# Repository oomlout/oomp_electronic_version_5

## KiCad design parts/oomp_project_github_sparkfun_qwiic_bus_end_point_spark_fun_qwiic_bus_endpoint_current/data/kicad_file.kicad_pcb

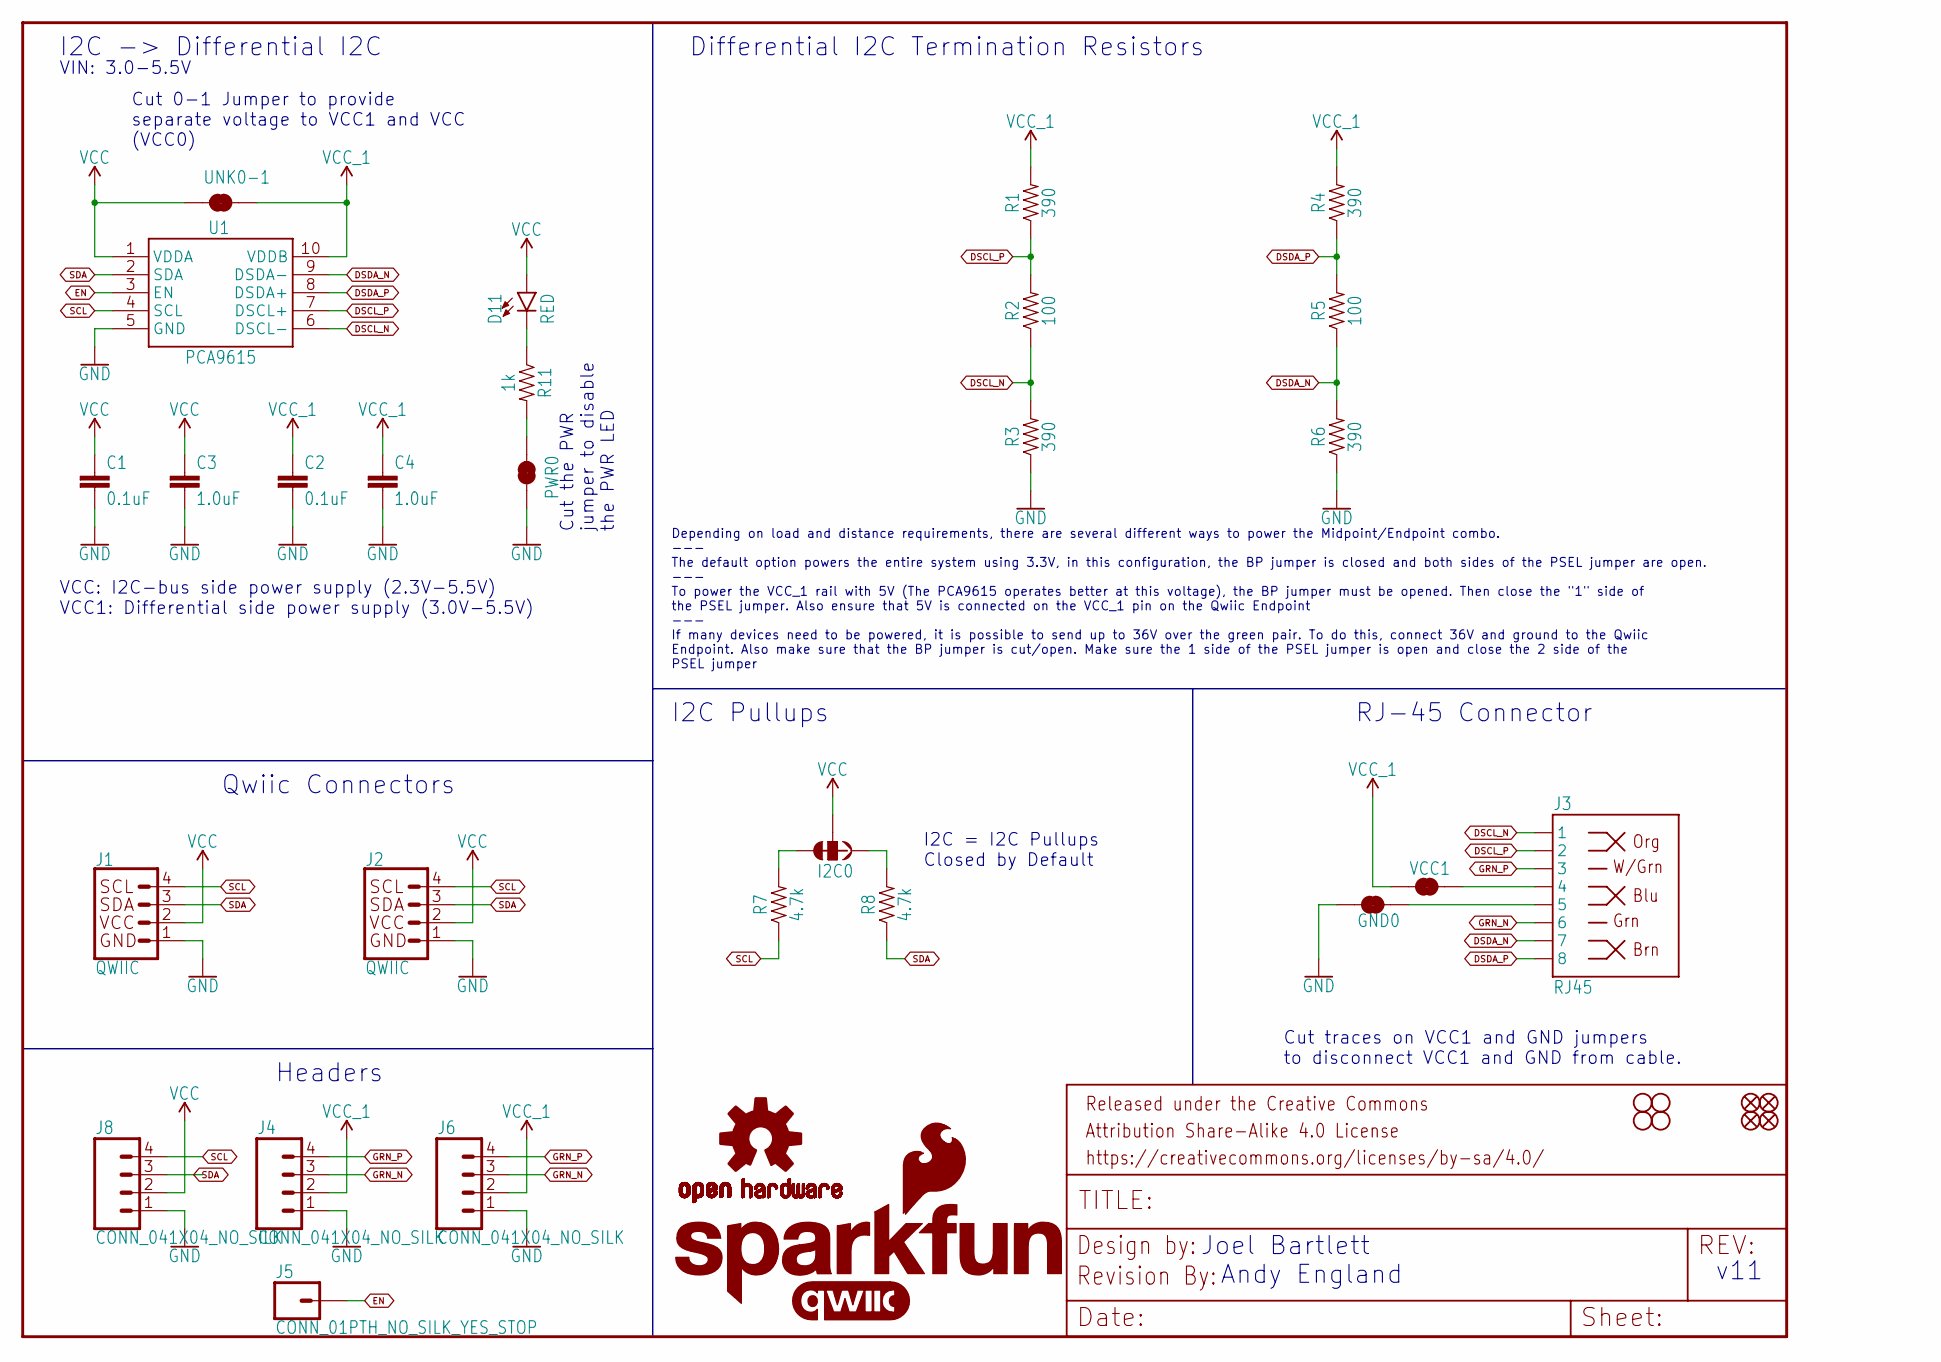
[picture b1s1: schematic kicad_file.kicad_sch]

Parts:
C1, C2: 0.1uF; 0603
C3, C4: 1.0uF; 0603
D11: RED; LED-0603
FD1, FD2, FD3, FD4: FIDUCIALUFIDUCIAL; FIDUCIAL-MICRO
FRAME1: FRAME-LETTER; CREATIVE_COMMONS
GND0: JUMPER-SMT_2_NC_TRACE_SILK; SMT-JUMPER_2_NC_TRACE_SILK
H1, H2, H3, H4: STAND-OFF
I2C0: JUMPER-SMT_3_2-NC_TRACE_SILK; SMT-JUMPER_3_2-NC_TRACE_SILK
J1, J2: QWIIC; JST04_1MM_RA
J3: RJ45; RJ45-8
J4, J6, J8: CONN_041X04_NO_SILK; 1X04_NO_SILK
J5: CONN_01PTH_NO_SILK_YES_STOP; 1X01_NO_SILK
LOGO1: OSHW-LOGOM; OSHW-LOGO-M
LOGO2: REVISION
LOGO3: QWIIC_LOGO_4MM; QWIIC_4MM
LOGO4: SFE_LOGO_NAME_FLAME.1_INCH; SFE_LOGO_NAME_FLAME_.1
LOGO5: SFE_LOGO_FLAME.1_INCH; SFE_LOGO_FLAME_.1
PWR0: JUMPER-SMT_2_NC_TRACE_SILK; SMT-JUMPER_2_NC_TRACE_SILK
R1, R3, R4, R6: 390; 0603
R2, R5: 100; 0603
R7, R8: 4.7k; 0603
R11: 1k; 0603
U1: PCA9615; TSSOP10
UNK0-1: JUMPER-SMT_2_NC_TRACE_SILK; SMT-JUMPER_2_NC_TRACE_SILK
VCC1: JUMPER-SMT_2_NC_TRACE_SILK; SMT-JUMPER_2_NC_TRACE_SILK

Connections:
DSCL_N: J3.1, R2.1, R3.2, U1.6 (DSCL-)
DSCL_P: J3.2, R1.1, R2.2, U1.7 (DSCL+)
DSDA_N: J3.7, R5.1, R6.2, U1.9 (DSDA-)
DSDA_P: J3.8, R4.1, R5.2, U1.8 (DSDA+)
EN: J5.1, U1.3 (EN)
GND: C1.2, C2.2, C3.2, C4.2, GND0.1, J1.1, J2.1, J4.1, J6.1, J8.1, PWR0.1, R3.1, R6.1, U1.5 (GND)
GRN_N: J3.6, J4.3, J6.3
GRN_P: J3.3, J4.4, J6.4
unnamed: J3.4, VCC1.2
unnamed: GND0.2, J3.5
unnamed: I2C0.1, R8.2
unnamed: I2C0.3, R7.2
unnamed: D11.C, R11.1
unnamed: PWR0.2, R11.2
SCL: J1.4, J2.4, J8.4, R7.1, U1.4 (SCL)
SDA: J1.3, J2.3, J8.3, R8.1, U1.2 (SDA)
VCC: C1.1, C3.1, D11.A, I2C0.2, J1.2, J2.2, J8.2, U1.1 (VDDA), UNK0-1.2
VCC_1: C2.1, C4.1, J4.2, J6.2, R1.2, R4.2, U1.10 (VDDB), UNK0-1.1, VCC1.1

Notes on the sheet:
Cut 0-1 Jumper to provide separate voltage to VCC1 and VCC (VCC0)
Joel Bartlett
VIN: 3.0-5.5V
I2C -> Differential I2C
RJ-45 Connector
Depending on load and distance requirements, there are several different ways to power the Midpoint/Endpoint combo. --- The default option powers the entire system using 3.3V, in this configuration, the BP jumper is closed and both sides of the PSEL jumper are open. --- To power the VCC_1 rail with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
Andy England
Qwiic Connectors
VCC: I2C-bus side power supply (2.3V-5.5V) VCC1: Differential side power supply (3.0V-5.5V)
Cut traces on VCC1 and GND jumpers to disconnect VCC1 and GND from cable.
Cut the PWR jumper to disable the PWR LED
Differential I2C Termination Resistors
Headers
I2C Pullups
v11
I2C = I2C Pullups Closed by Default

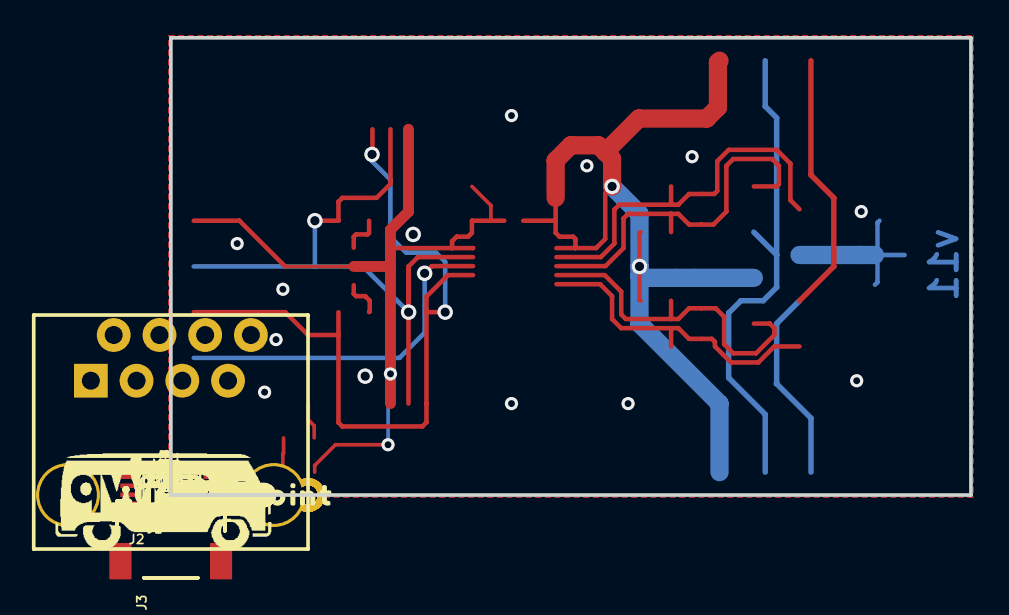
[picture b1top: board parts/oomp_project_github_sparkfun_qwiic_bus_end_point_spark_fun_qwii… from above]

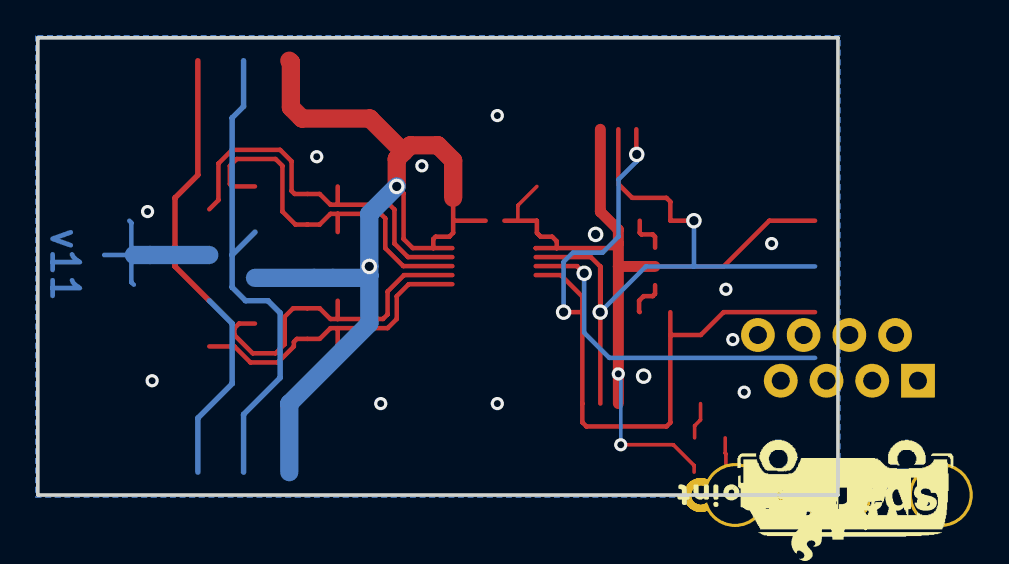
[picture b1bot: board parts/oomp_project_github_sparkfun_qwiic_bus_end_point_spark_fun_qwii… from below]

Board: 2 copper layers, 44.5 x 25.4 mm, 76 parts (23 on the bottom side), 18 nets.

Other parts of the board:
U$1: I2C
U$2, U$29: GRN0
U$3, U$4, U$5, U$6, U$13, U$33, U$34: #GND#0
U$7, U$8: #3V3#0
U$9, U$15: #SDA#0
U$10, U$16: #SCL#0
U$11, U$17: #EN#0
U$12: #VDDA#0
U$14, U$18: #GND2#0
U$19, U$22: #GRNW#0
U$20, U$21, U$31, U$32: #VCC1#0
U$23, U$28: QWIICBUS#WORKING#LOGO#JPG
U$24, U$30: #VCC2#0
U$25: 0#10
U$26, U$35: ENDPOINT0
U$27: PWR0

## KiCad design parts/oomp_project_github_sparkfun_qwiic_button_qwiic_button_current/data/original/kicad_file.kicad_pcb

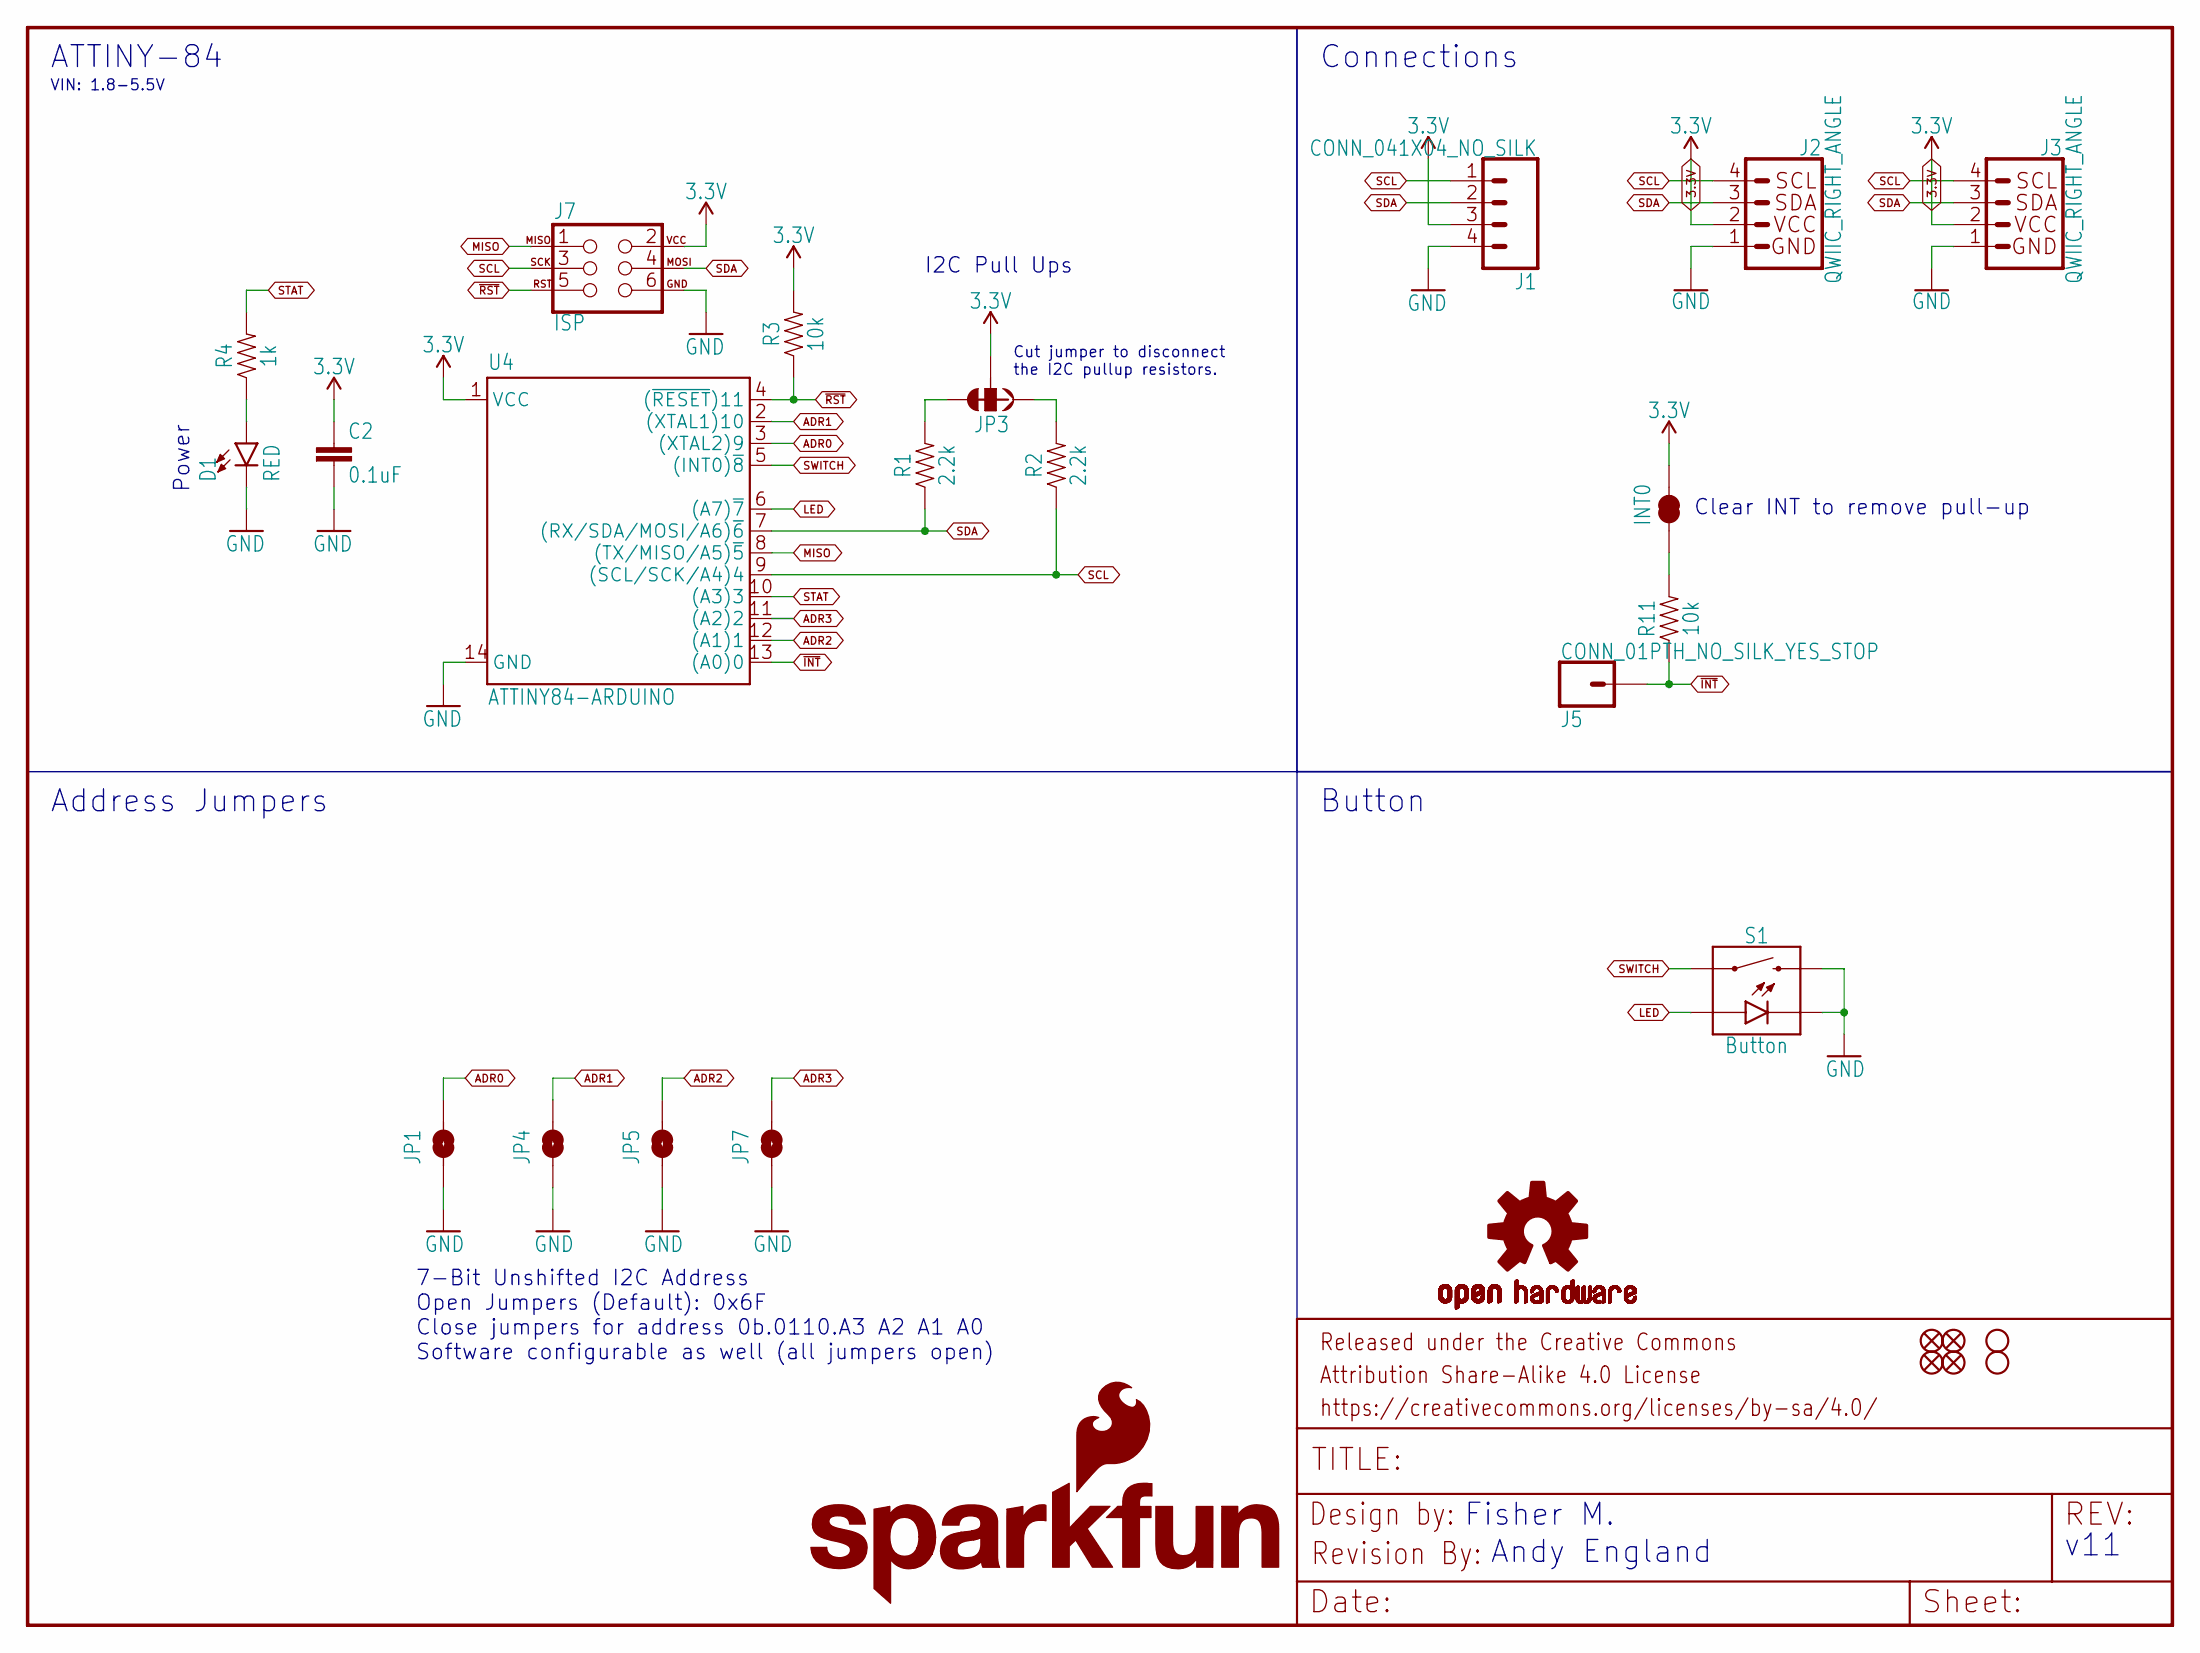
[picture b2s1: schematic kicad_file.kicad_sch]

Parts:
C2: 0.1uF; 0603
D1: RED; LED-0603
FRAME1: FRAME-LETTER; CREATIVE_COMMONS
H1, H2: STAND-OFF
INT0: JUMPER-SMT_2_NC_TRACE_SILK; SMT-JUMPER_2_NC_TRACE_SILK
J1: CONN_041X04_NO_SILK; 1X04_NO_SILK
J2, J3: QWIIC_RIGHT_ANGLE; JST04_1MM_RA
J5: CONN_01PTH_NO_SILK_YES_STOP; 1X01_NO_SILK
J7: ISP; 2X3_TEST_POINTS
JP1, JP4, JP5, JP7: JUMPER-SMT_2_NO_NO-SILK; SMT-JUMPER_2_NO_NO-SILK
JP2, JP6, JP8, JP9: FIDUCIALUFIDUCIAL; MICRO-FIDUCIAL
JP3: JUMPER-SMT_3_2-NC_TRACE_SILK; SMT-JUMPER_3_2-NC_TRACE_SILK
LOGO1: OSHW-LOGOMINI; OSHW-LOGO-MINI
LOGO2: REVISION
LOGO3: SFE_LOGO_NAME.1_INCH; SFE_LOGO_NAME_.1
LOGO4: SFE_LOGO_FLAME.1_INCH; SFE_LOGO_FLAME_.1
R1, R2: 2.2k; 0603
R3, R11: 10k; 0603
R4: 1k; 0603
S1: Button; TACTILE_SWITCH_LED_PTH_12MM
U4: ATTINY84-ARDUINO; SO14

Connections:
3.3V: C2.1, INT0.2, J1.3, J2.2, J3.2, J7.2, JP3.2, R3.2, U4.1 (VCC)
ADR0: JP1.2, U4.3 ((XTAL2)9)
ADR1: JP4.2, U4.2 ((XTAL1)10)
ADR2: JP5.2, U4.12 ((A1)1)
ADR3: JP7.2, U4.11 ((A2)2)
GND: C2.2, D1.C, J1.4, J2.1, J3.1, J7.6, JP1.1, JP4.1, JP5.1, JP7.1, S1.2, S1.C, U4.14 (GND)
INT_R: INT0.1, R11.2
LED: S1.A, U4.6 ((A7)~7)
MISO: J7.1, U4.8 ((TX/MISO/A5)~5)
unnamed: D1.A, R4.1
SCL: J1.1, J2.4, J3.4, J7.3, R2.1, U4.9 ((SCL/SCK/A4)4)
SCL_PU1: JP3.1, R2.2
SDA: J1.2, J2.3, J3.3, J7.4, R1.1, U4.7 ((RX/SDA/MOSI/A6)~6)
SDA_PU1: JP3.3, R1.2
STAT: R4.2, U4.10 ((A3)3)
SWITCH: S1.4 (1), U4.5 ((INT0)~8)
~INT: J5.1, R11.1, U4.13 ((A0)0)
~RST: J7.5, R3.1, U4.4 ((~RESET)11)

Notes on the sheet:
Andy England
Fisher M.
7-Bit Unshifted I2C Address Open Jumpers (Default): 0x6F Close jumpers for address 0b.0110.A3 A2 A1 A0 Software configurable as well (all jumpers open)
I2C Pull Ups
Cut jumper to disconnect the I2C pullup resistors.
Clear INT to remove pull-up
ATTINY-84
VIN: 1.8-5.5V
Button
Power
Address Jumpers
v11
Connections

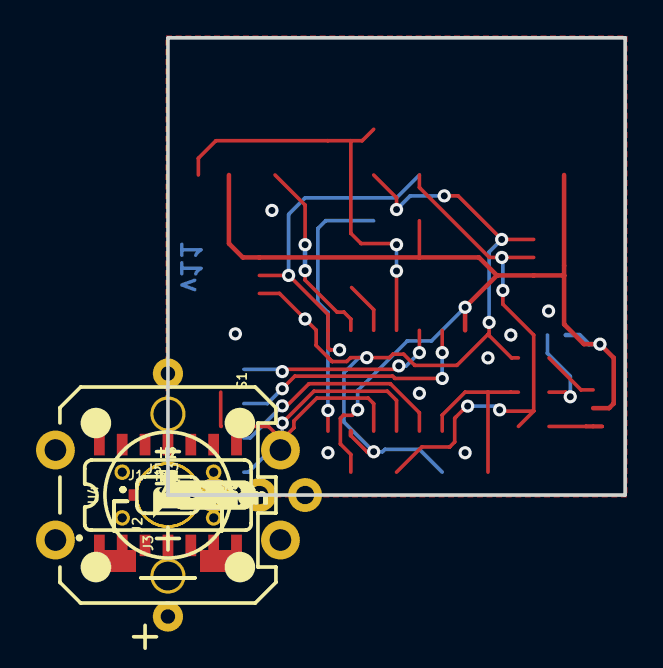
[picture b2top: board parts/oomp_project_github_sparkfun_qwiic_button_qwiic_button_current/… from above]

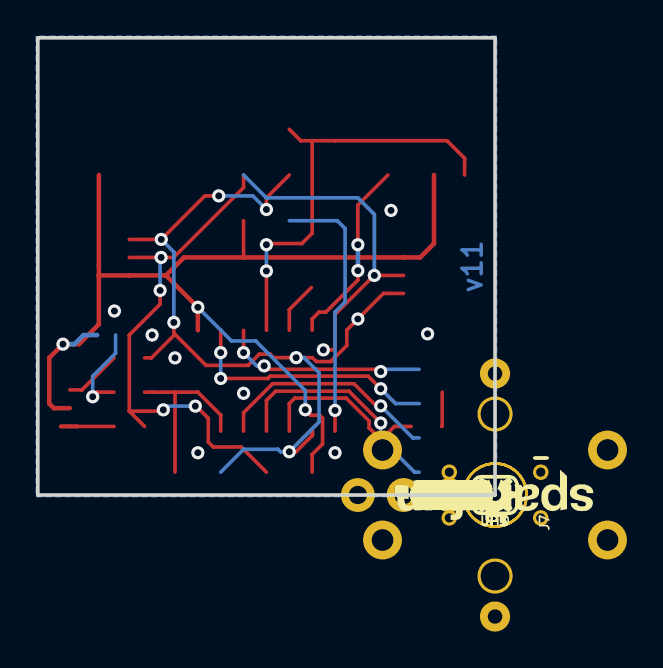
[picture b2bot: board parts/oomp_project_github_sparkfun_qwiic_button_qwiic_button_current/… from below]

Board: 2 copper layers, 25.4 x 25.4 mm, 48 parts (23 on the bottom side), 18 nets.

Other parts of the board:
U$1, U$2: BUTTON1
U$3: PWR-()-04
U$4: INT-()-04
U$5: SCL
U$6: SDA
U$7: 3.3V
U$8: GND
U$9: (ADR)
U$10: I_SUPER2_C-()-03
U$15: INT#-[_-04
U$16: A00
U$17: A11
U$19: A22
U$20, U$23: QWIIC0
U$21: A33

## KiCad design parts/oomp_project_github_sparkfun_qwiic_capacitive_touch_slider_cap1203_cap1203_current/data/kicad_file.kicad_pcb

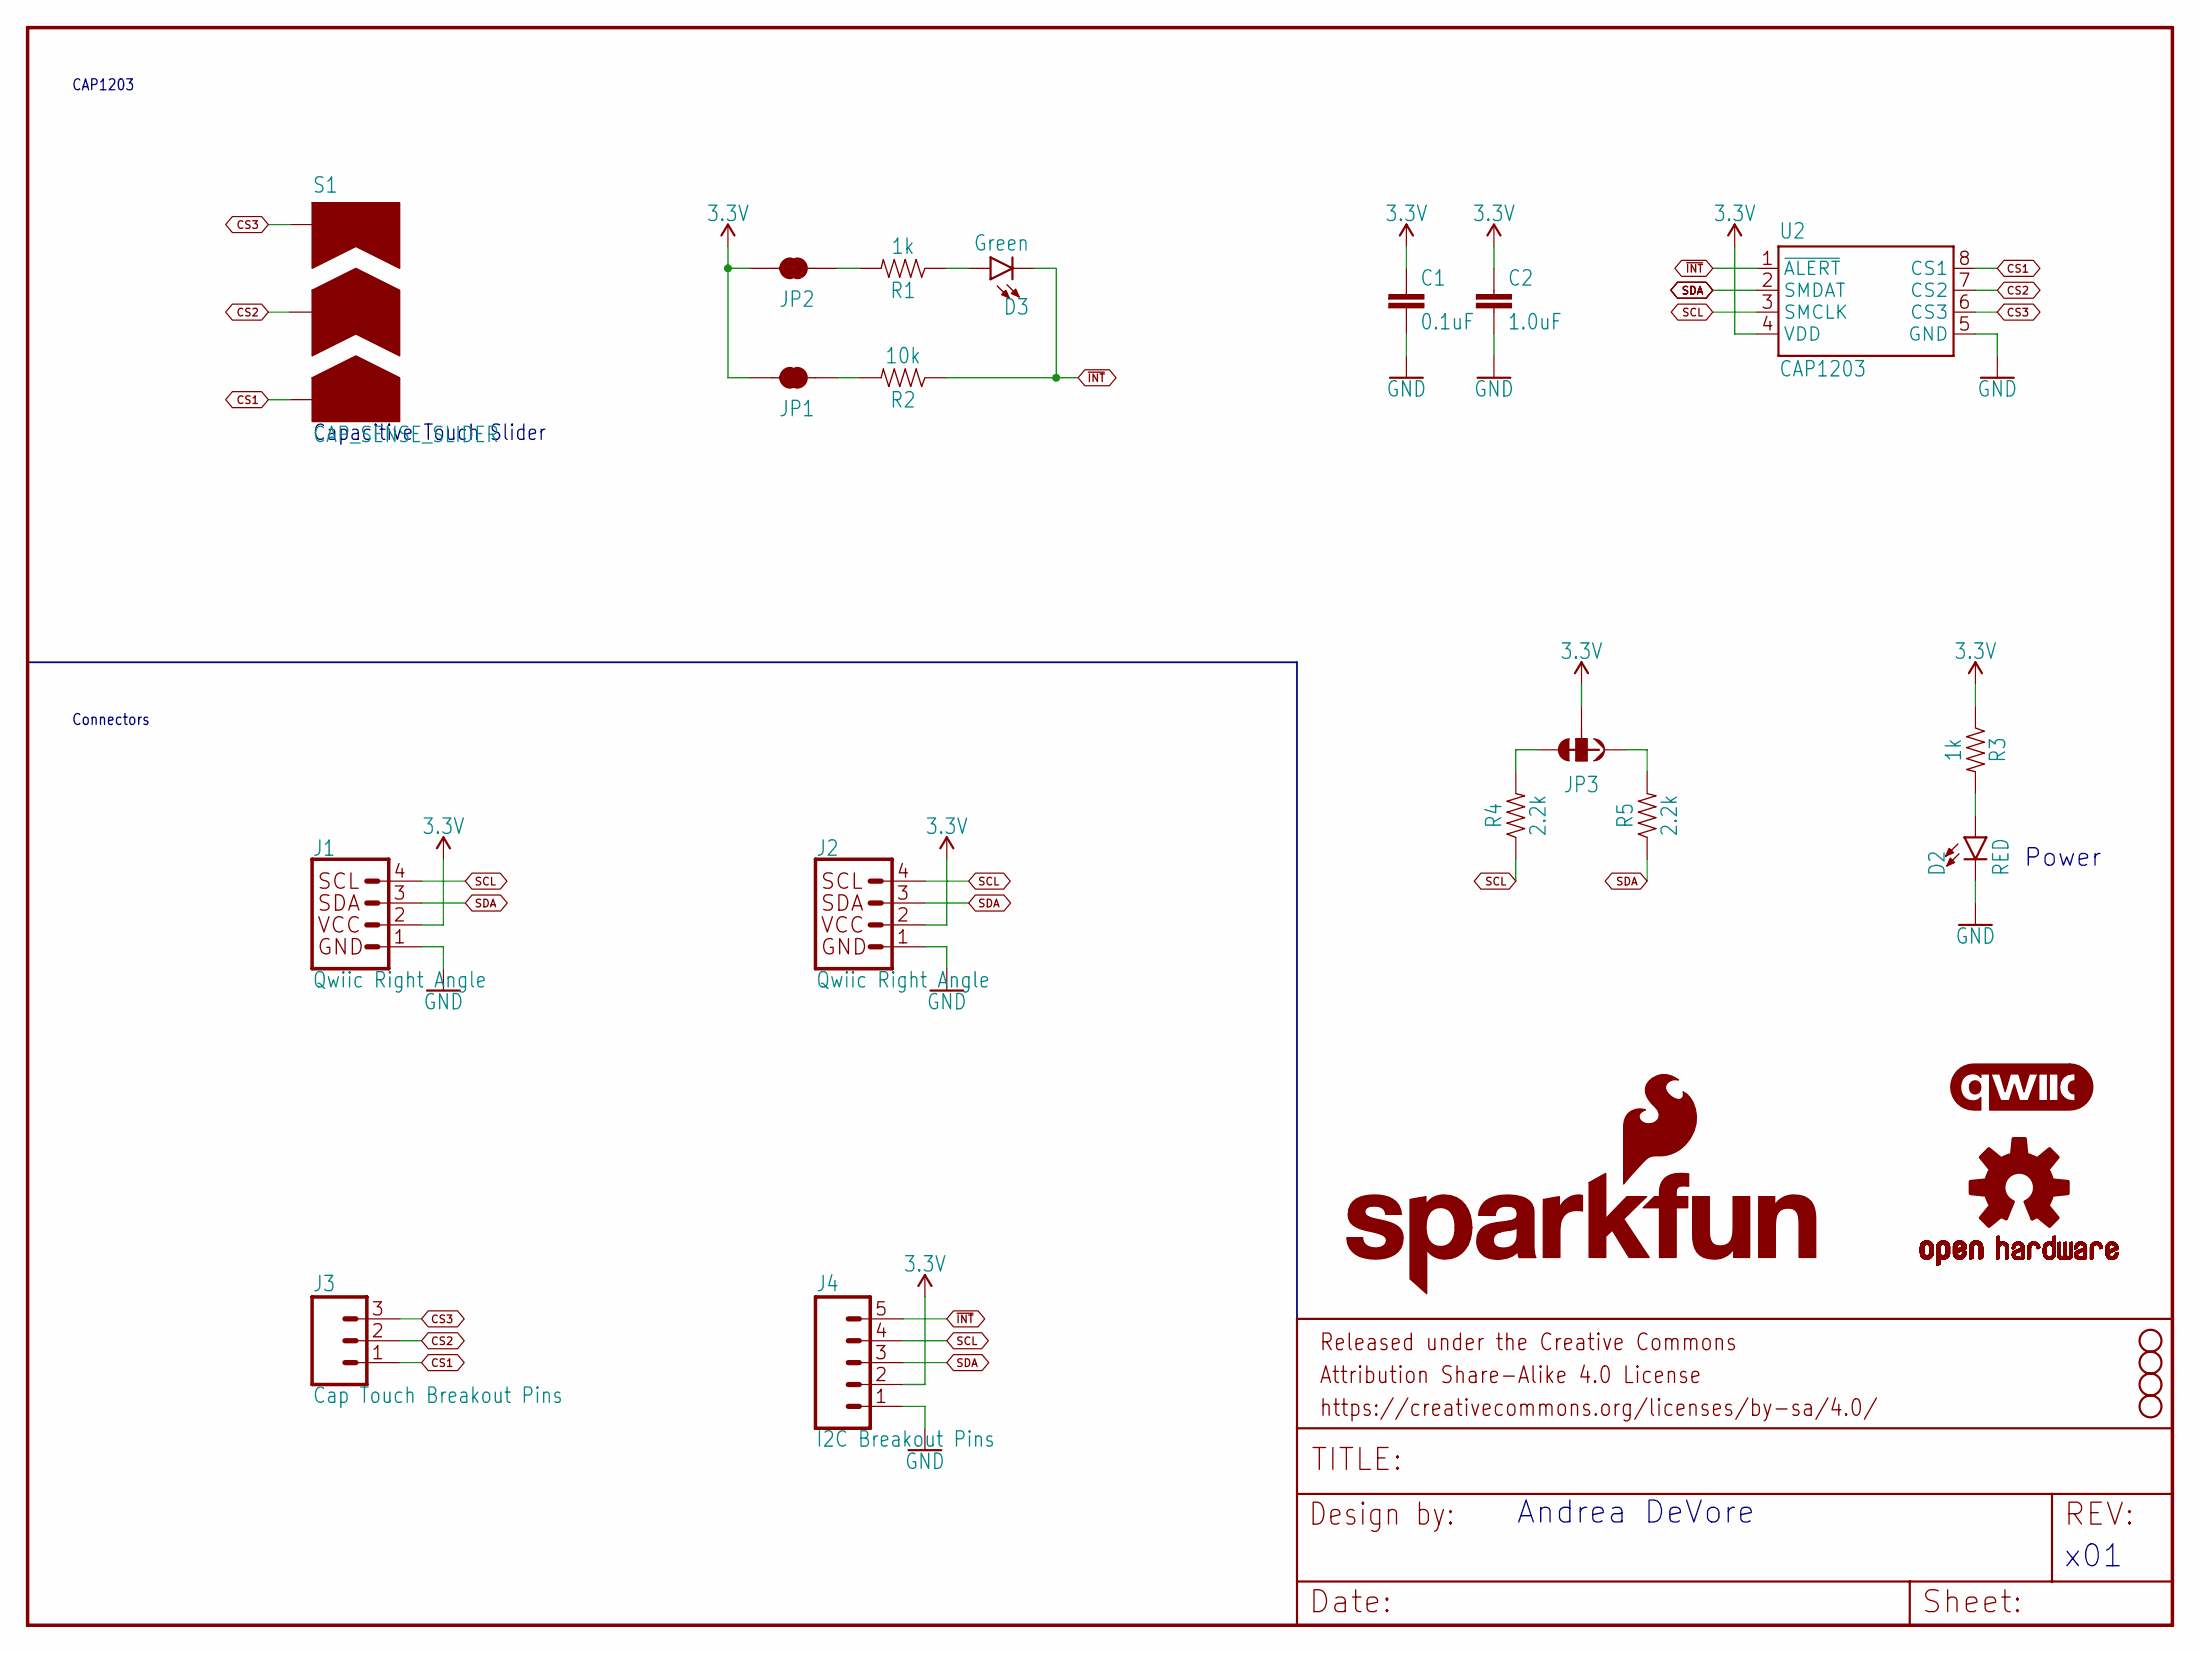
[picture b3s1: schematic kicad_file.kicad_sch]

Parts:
C1: 0.1uF; 0603
C2: 1.0uF; 0603
D2: RED; LED-0603
D3: Green; LED-1206-BOTTOM
FRAME1: FRAME-LETTER; CREATIVE_COMMONS
H1, H2, H3, H5: STAND-OFF
J1, J2: Qwiic Right Angle; JST04_1MM_RA
J3: Cap Touch Breakout Pins; 1X03_NO_SILK
J4: I2C Breakout Pins; 1X05_NO_SILK
JP1, JP2: JUMPER-SMT_2_NC_TRACE_SILK; SMT-JUMPER_2_NC_TRACE_SILK
JP3: JUMPER-SMT_3_2-NC_TRACE_SILK; SMT-JUMPER_3_2-NC_TRACE_SILK
LOGO1: SFE_LOGO_NAME_FLAME.1_INCH; SFE_LOGO_NAME_FLAME_.1
LOGO3: OSHW-LOGOS; OSHW-LOGO-S
R1, R3: 1k; 0603
R2: 10k; 0603
R4, R5: 2.2k; 0603
S1: CAP_SENSE_SLIDER
U2: CAP1203; SO08-TIGHT
U$17: QWIIC_LOGO_5MM; QWIIC_5MM

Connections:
3.3V: C1.1, C2.1, J1.2, J2.2, J4.2, JP1.2, JP2.2, JP3.2, R3.1, U2.4 (VDD)
CS1: J3.1, S1.1, U2.8 (CS1)
CS2: J3.2, S1.2, U2.7 (CS2)
CS3: J3.3, S1.3, U2.6 (CS3)
GND: C1.2, C2.2, D2.C, J1.1, J2.1, J4.1, U2.5 (GND)
unnamed: JP1.1, R2.2
unnamed: D2.A, R3.2
unnamed: JP2.1, R1.2
unnamed: JP3.3, R4.2
unnamed: JP3.1, R5.2
unnamed: D3.A, R1.1
SCL: J1.4, J2.4, J4.4, R4.1, U2.3 (SMCLK)
SDA: J1.3, J2.3, J4.3, R5.1, U2.2 (SMDAT)
~INT: D3.C, J4.5, R2.1, U2.1 (~ALERT)

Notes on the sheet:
Andrea DeVore
Connectors
Capacitive Touch Slider
x01
CAP1203
Power

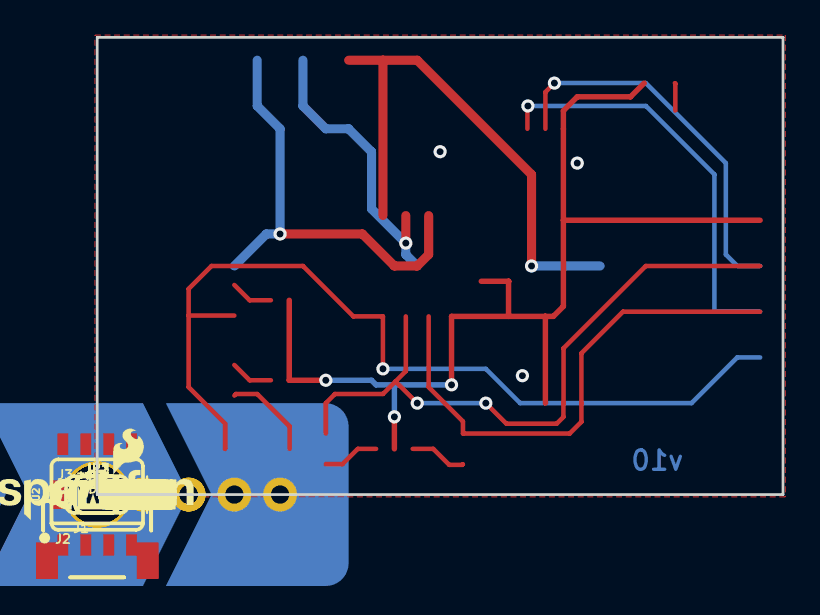
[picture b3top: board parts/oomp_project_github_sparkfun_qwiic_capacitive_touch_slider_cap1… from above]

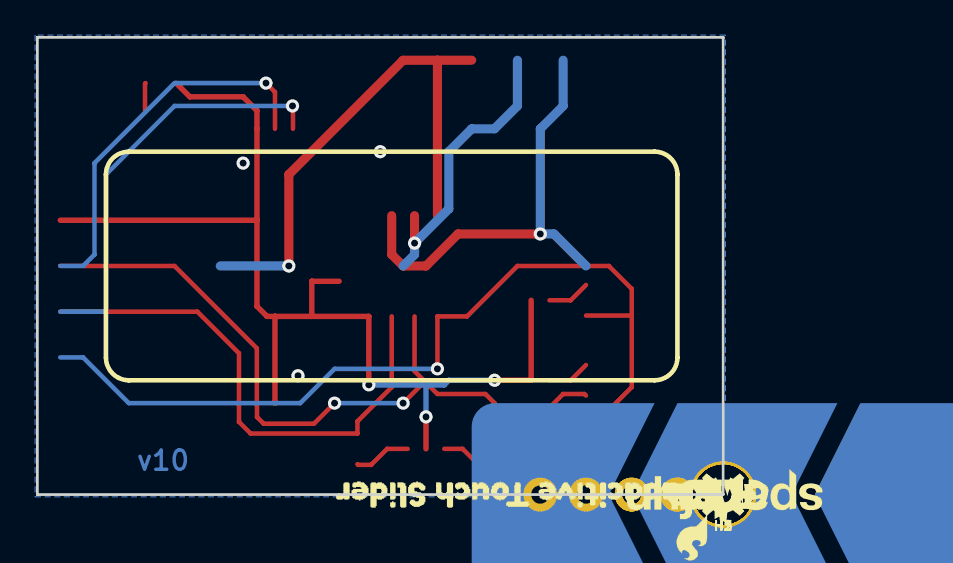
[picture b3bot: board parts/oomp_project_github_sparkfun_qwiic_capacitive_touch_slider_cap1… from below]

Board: 2 copper layers, 38.1 x 25.4 mm, 42 parts (10 on the bottom side), 14 nets.

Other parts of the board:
LOGO2: SFE_LOGO_NAME_FLAME.1_INCH; SFE_LOGO_NAME_FLAME_.1
U$1: 3V3-04
U$2: GND-04
U$4: QWIIC_LOGO_5MM; QWIIC_5MM
U$5, U$14: INT0
U$7: #INT5
U$8: SCL3
U$9: SDA4
U$10: CS10
U$11: CS21
U$12: CS32
U$13: I_SUPER2_C-()-03
U$15: PWR-()-03
U$16: LED0
U$18: CAPACITIVE_TOUCH_SLIDER0

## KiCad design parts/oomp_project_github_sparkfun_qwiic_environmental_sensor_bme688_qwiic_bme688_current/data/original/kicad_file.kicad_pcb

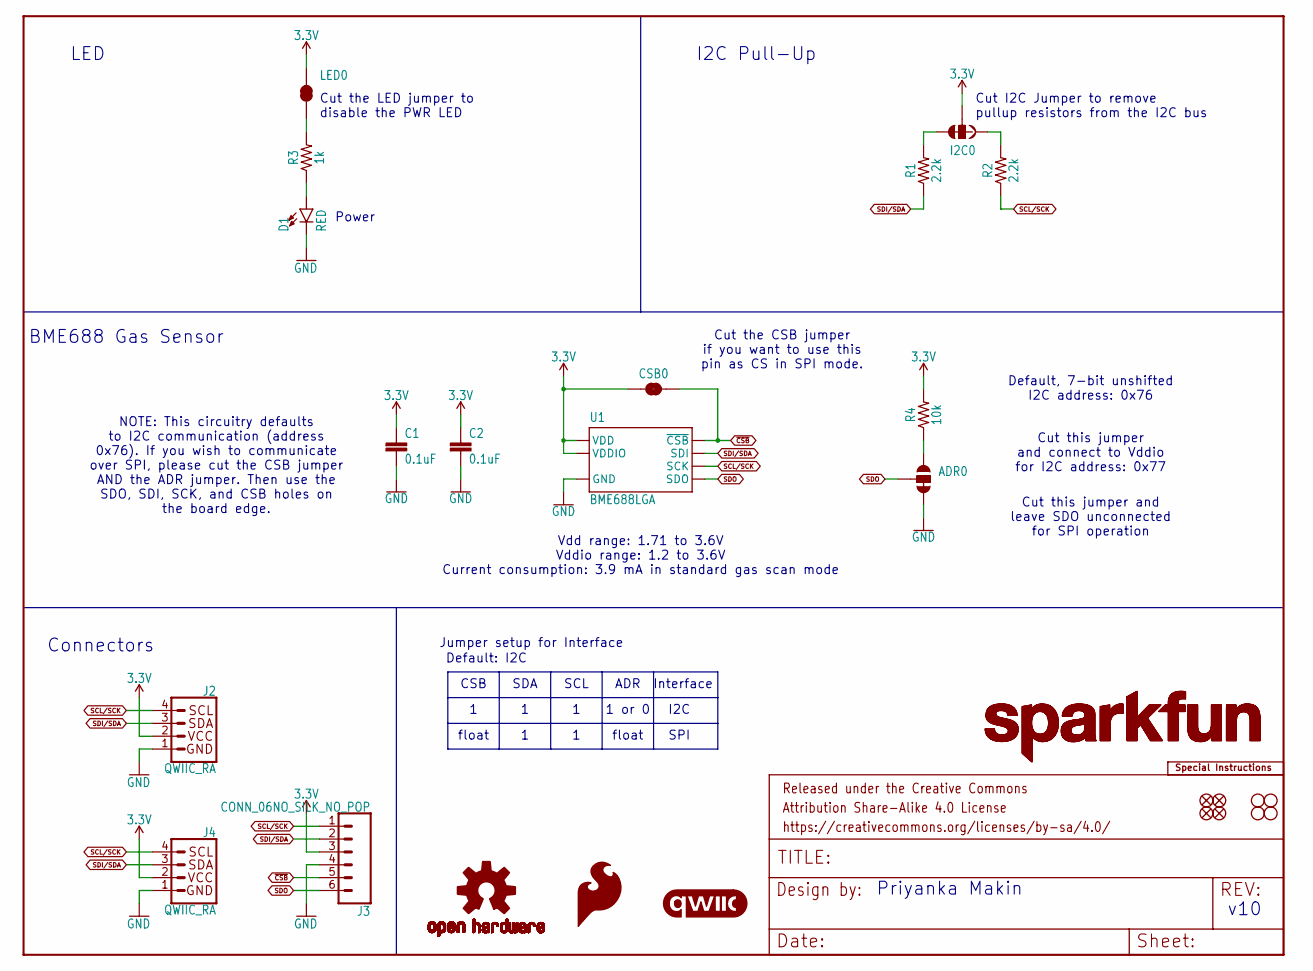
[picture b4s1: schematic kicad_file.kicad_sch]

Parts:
ADR0: JUMPER-SMT_3_1-NC_TRACE_SILK; SMT-JUMPER_3_1-NC_TRACE_SILK
C1, C2: 0.1uF; 0603
CSB0: JUMPER-SMT_2_NC_TRACE_SILK; SMT-JUMPER_2_NC_TRACE_SILK
D1: RED; LED-0603
FRAME1: FRAME-LETTER; CREATIVE_COMMONS
I2C0: JUMPER-SMT_3_2-NC_TRACE_SILK; SMT-JUMPER_3_2-NC_TRACE_SILK
J2, J4: QWIIC_RA; JST04_1MM_RA
J3: CONN_06NO_SILK_NO_POP; 1X06_NO_SILK
JP1, JP2, JP5, JP6: FIDUCIALUFIDUCIAL; FIDUCIAL-MICRO
JP3, JP4, JP7, JP8: STAND-OFF
LED0: JUMPER-SMT_2_NC_TRACE_SILK; SMT-JUMPER_2_NC_TRACE_SILK
LOGO1: SPECIAL_INSTRUCTIONS-ORDERING; ORDERING_INSTRUCTIONS
LOGO2: QWIIC_LOGO_5MM; QWIIC_5MM
LOGO3, LOGO6: SFE_LOGO_NAME.1_INCH; SFE_LOGO_NAME_.1
LOGO4: SFE_LOGO_FLAME.1_INCH; SFE_LOGO_FLAME_.1
LOGO5: OSHW-LOGOS; OSHW-LOGO-S
R1, R2: 2.2k; 0603
R3: 1k; 0603
R4: 10k; 0603
U1: BME688LGA; LGA_8PIN

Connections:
3.3V: C1.1, C2.1, CSB0.1, I2C0.2, J2.2, J3.3, J4.2, LED0.2, R4.2, U1.6 (VDDIO), U1.8 (VDD)
GND: ADR0.3, C1.2, C2.2, D1.C, J2.1, J3.4, J4.1, U1.1 (GND), U1.7 (GND)
unnamed: LED0.1, R3.2
unnamed: I2C0.3, R1.2
unnamed: D1.A, R3.1
unnamed: I2C0.1, R2.2
unnamed: ADR0.1, R4.1
SCL/SCK: J2.4, J3.1, J4.4, R2.1, U1.4 (SCK)
SDI/SDA: J2.3, J3.2, J4.3, R1.1, U1.3 (SDI)
SDO: ADR0.2, J3.6, U1.5 (SDO)
~CSB: CSB0.2, J3.5, U1.2 (~CSB)

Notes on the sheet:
Priyanka Makin
Cut the LED jumper to disable the PWR LED
Cut this jumper and connect to Vddio for I2C address: 0x77
float
LED
v10
1 or 0
NOTE: This circuitry defaults to I2C communication (address 0x76). If you wish to communicate over SPI, please cut the CSB jumper AND the ADR jumper. Then use the SDO, SDI, SCK, and CSB holes on the board edge.
Cut I2C Jumper to remove pullup resistors from the I2C bus
Default: I2C
BME688 Gas Sensor
I2C
Jumper setup for Interface
Interface
Connectors
Cut this jumper and leave SDO unconnected for SPI operation~{}
SCL
ADR
Power
SPI
SDA
Vdd range: 1.71 to 3.6V Vddio range: 1.2 to 3.6V Current consumption: 3.9 mA in standard gas scan mode
I2C Pull-Up
Default, 7-bit unshifted I2C address: 0x76
Cut the CSB jumper if you want to use this pin as CS in SPI mode.
CSB

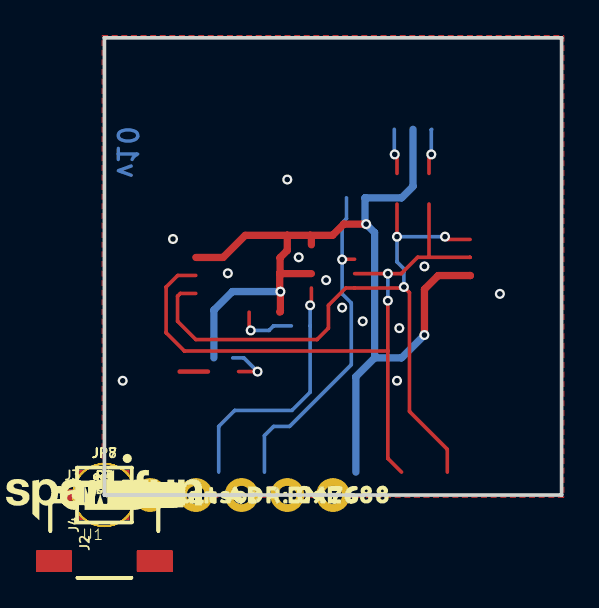
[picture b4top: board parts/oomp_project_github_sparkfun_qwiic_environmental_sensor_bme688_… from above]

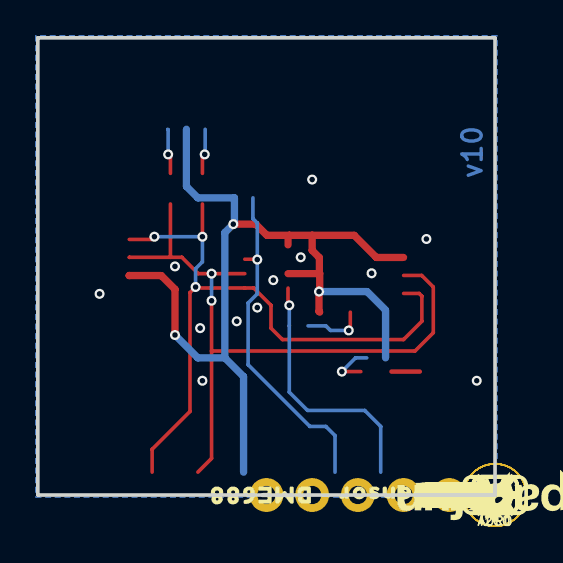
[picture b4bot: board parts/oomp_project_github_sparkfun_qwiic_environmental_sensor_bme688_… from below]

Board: 2 copper layers, 25.4 x 25.4 mm, 52 parts (22 on the bottom side), 11 nets.

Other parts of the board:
U$1, U$33: #GND#0
U$2, U$16: #SDO#0
U$3: #CSB#0
U$5: PWR0
U$6: #I2C#0
U$7, U$10: GAS_SENSOR_#_BME6880
U$8: #LED#0
U$9: 0X760
U$11: #ADR#0
U$12: DEFAULT_ADR#_0X760
U$13: 0X770
U$14, U$15: #3V3#0
U$19: #SDI#0
U$20: #SCK#0
U$21, U$22: ##CSB##0
U$35: #SDA#0
U$36: #SCL#0

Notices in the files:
parts/oomp_project_github_sparkfun_qwiic_bus_end_point_spark_fun_qwiic_bus_endpoint_current/data/original/kicad_file.kicad_sch:
Released under the Creative Commons
https://creativecommons.org/licenses/by-sa/4.0
parts and their libraries:
Released under the Creative Commons Attribution Share-Alike 4.0 License
